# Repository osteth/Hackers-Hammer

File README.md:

# Hackers-Hammer
Hardware Hacking Multi-tool

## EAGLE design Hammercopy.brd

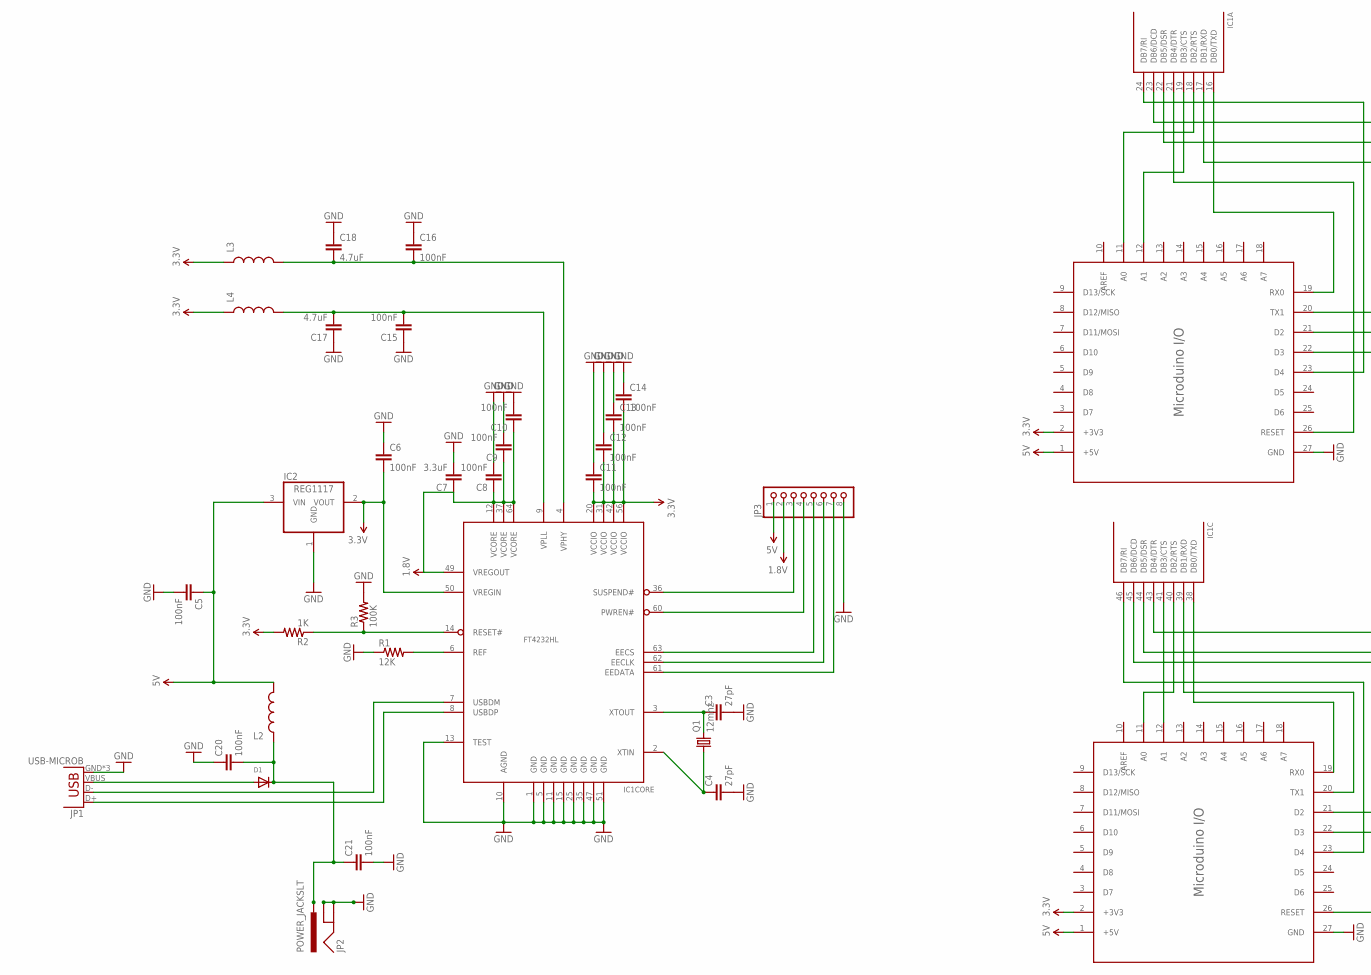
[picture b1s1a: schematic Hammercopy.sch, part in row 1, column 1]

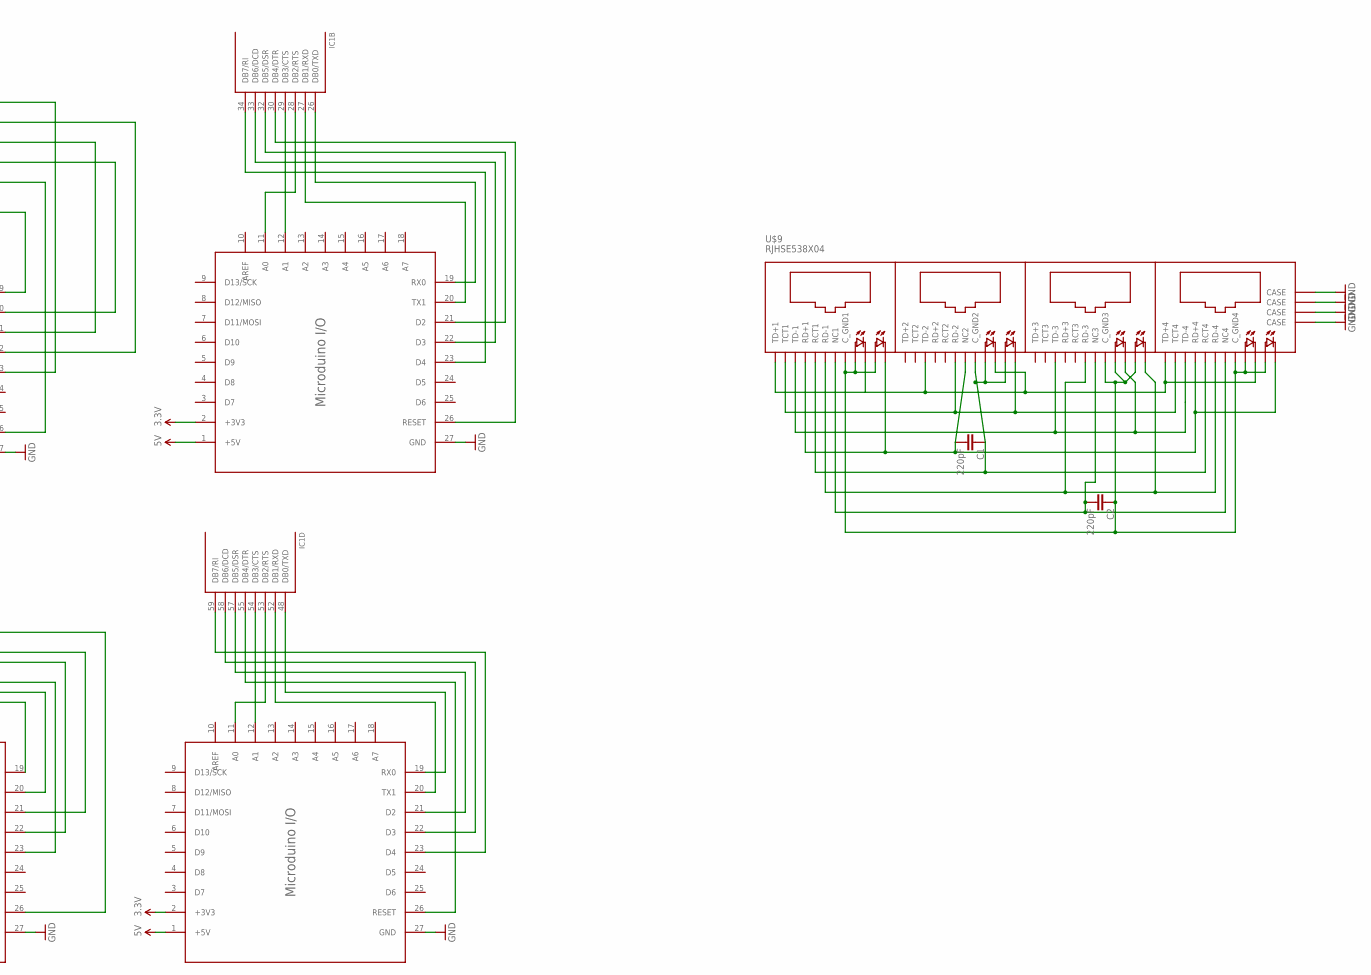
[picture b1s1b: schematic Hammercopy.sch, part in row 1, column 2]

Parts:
C1, C2: 220pF; 0402-CAP
C3, C4: 27pF; 0402-CAP
C5, C6, C8, C9, C10, C11, C12, C13, C14, C15, C16, C20, C21: 100nF; 0402-CAP
C7: 3.3uF; 0402-CAP
C17, C18: 4.7uF; 0402-CAP
D1: DIODESMA; SMADIODE
IC1: FT4232HL; LQFP64
IC2: REG1117; SOT223
JP1: USB-MICROB
JP2: POWER_JACKSLT; POWER_JACK_SLOT
JP3: PINHD-1X8BIG; 1X08-BIG
L2, L3, L4: INDUCTOR1206H*; INDUCTOR-1206
Q1: 12mhz; HC49UP
R1: 12K; 0402-RES
R2: 1K; 0402-RES
R3: 100K; 0402-RES
U$5, U$6, U$7, U$8: MICRODUINO_PING-MICRDUINO/1009-TEST; MICRODUINO_PIN-MICRODUINO-1009-TEST
U$9: RJHSE538X04

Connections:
1.8V: C7.1, C8.1, C9.1, C10.1, IC1.12 (VCORE), IC1.37 (VCORE), IC1.49 (VREGOUT), IC1.64 (VCORE), JP3.2
3.3V: C6.2, C11.2, C12.2, C13.2, C14.2, IC1.20 (VCCIO), IC1.31 (VCCIO), IC1.42 (VCCIO), IC1.56 (VCCIO), IC2.2 (VOUT), L3.P$1 (1), L4.P$1 (1), R2.2, U$5.2 (+3V3), U$6.2 (+3V3), U$7.2 (+3V3), U$8.2 (+3V3)
5V: C5.1, IC2.3 (VIN), JP3.1, L2.P$2 (2), U$5.1 (+5V), U$6.1 (+5V), U$7.1 (+5V), U$8.1 (+5V)
ASDF: C2.1, U$9.1-8 (C_GND1), U$9.1-10 (A2), U$9.1-12 (A1), U$9.3-8 (C_GND3), U$9.3-10 (A6), U$9.3-12 (A5)
GND: C3.2, C4.2, C5.2, C6.1, C7.2, C8.2, C9.2, C10.2, C11.1, C12.1, C13.1, C14.1, C15.1, C16.1, C17.1, C18.1, C20.1, C21.2, IC1.1 (GND), IC1.5 (GND), IC1.10 (AGND), IC1.11 (GND), IC1.13 (TEST), IC1.15 (GND), IC1.25 (GND), IC1.35 (GND), IC1.47 (GND), IC1.51 (GND), IC2.1 (GND), JP1.GND, JP1.MT1 (GND), JP1.MT2 (GND), JP2.GND@1 (GNDBREAK), JP2.GND@2 (GND), JP3.8, R1.1, R3.2, U$5.27 (GND), U$6.27 (GND), U$7.27 (GND), U$8.27 (GND), U$9.CASE@1 (CASE), U$9.CASE@2 (CASE), U$9.CASE@3 (CASE), U$9.CASE@4 (CASE)
INJECT: U$9.1-1 (TD+1), U$9.1-11 (C1), U$9.2-3 (TD-2), U$9.2-11 (C3)
unnamed: IC1.34 (DB7/RI), U$7.23 (D4)
unnamed: IC1.30 (DB4/DTR), U$7.26 (RESET)
unnamed: IC1.32 (DB5/DSR), U$7.21 (D2)
unnamed: IC1.21 (DB4/DTR), U$5.26 (RESET)
unnamed: IC1.16 (DB0/TXD), U$5.19 (RX0)
unnamed: IC1.41 (DB3/CTS), U$8.12 (A1)
unnamed: IC1.40 (DB2/RTS), U$8.11 (A0)
unnamed: IC1.7 (USBDM), JP1.D-
unnamed: IC1.6 (REF), R1.2
unnamed: IC1.14 (RESET#), R2.1, R3.1
unnamed: IC1.39 (DB1/RXD), U$8.20 (TX1)
unnamed: IC1.38 (DB0/TXD), U$8.19 (RX0)
unnamed: IC1.46 (DB7/RI), U$8.23 (D4)
unnamed: IC1.45 (DB6/DCD), U$8.22 (D3)
unnamed: IC1.36 (SUSPEND#), JP3.3
unnamed: IC1.60 (PWREN#), JP3.4
unnamed: IC1.17 (DB1/RXD), U$5.20 (TX1)
unnamed: IC1.63 (EECS), JP3.5
unnamed: IC1.62 (EECLK), JP3.6
unnamed: IC1.61 (EEDATA), JP3.7
unnamed: IC1.33 (DB6/DCD), U$7.22 (D3)
unnamed: IC1.18 (DB2/RTS), U$5.11 (A0)
unnamed: IC1.19 (DB3/CTS), U$5.12 (A1)
unnamed: IC1.22 (DB5/DSR), U$5.21 (D2)
unnamed: IC1.23 (DB6/DCD), U$5.22 (D3)
unnamed: IC1.24 (DB7/RI), U$5.23 (D4)
unnamed: IC1.44 (DB5/DSR), U$8.21 (D2)
unnamed: IC1.29 (DB3/CTS), U$7.12 (A1)
unnamed: IC1.28 (DB2/RTS), U$7.11 (A0)
unnamed: IC1.26 (DB0/TXD), U$7.19 (RX0)
unnamed: IC1.27 (DB1/RXD), U$7.20 (TX1)
unnamed: IC1.43 (DB4/DTR), U$8.26 (RESET)
unnamed: IC1.54 (DB3/CTS), U$6.12 (A1)
unnamed: IC1.53 (DB2/RTS), U$6.11 (A0)
unnamed: D1.A, JP1.VBUS
unnamed: U$9.1-2 (TCT1), U$9.2-6 (RD-2), U$9.2-9 (C4)
unnamed: U$9.1-3 (TD-1), U$9.3-3 (TD-3), U$9.3-11 (C5)
unnamed: C3.1, IC1.3 (XTOUT), Q1.2
unnamed: C4.1, IC1.2 (XTIN), Q1.1
unnamed: U$9.1-6 (RD-1), U$9.3-6 (RD-3), U$9.3-9 (C6)
unnamed: IC1.8 (USBDP), JP1.D+
unnamed: IC1.52 (DB1/RXD), U$6.20 (TX1)
unnamed: C1.2, U$9.1-4 (RD+1), U$9.1-9 (C2), U$9.2-7 (NC2)
unnamed: C1.1, U$9.1-5 (RCT1), U$9.2-8 (C_GND2)
unnamed: IC1.48 (DB0/TXD), U$6.19 (RX0)
unnamed: C2.2, U$9.1-7 (NC1), U$9.3-7 (NC3)
unnamed: IC1.55 (DB4/DTR), U$6.26 (RESET)
unnamed: IC1.57 (DB5/DSR), U$6.21 (D2)
unnamed: IC1.58 (DB6/DCD), U$6.22 (D3)
unnamed: IC1.59 (DB7/RI), U$6.23 (D4)
unnamed: U$9.4-1 (TD+4), U$9.4-11 (C7)
unnamed: C15.2, C17.2, IC1.9 (VPLL), L4.P$2 (2)
unnamed: C20.2, C21.1, D1.C, JP2.PWR, L2.P$1 (1)
unnamed: C16.2, C18.2, IC1.4 (VPHY), L3.P$2 (2)
unnamed: U$9.4-4 (RD+4), U$9.4-9 (C8)
unnamed: U$9.4-8 (C_GND4), U$9.4-10 (A8), U$9.4-12 (A7)
unnamed: U$9.2-10 (A4), U$9.2-12 (A3)

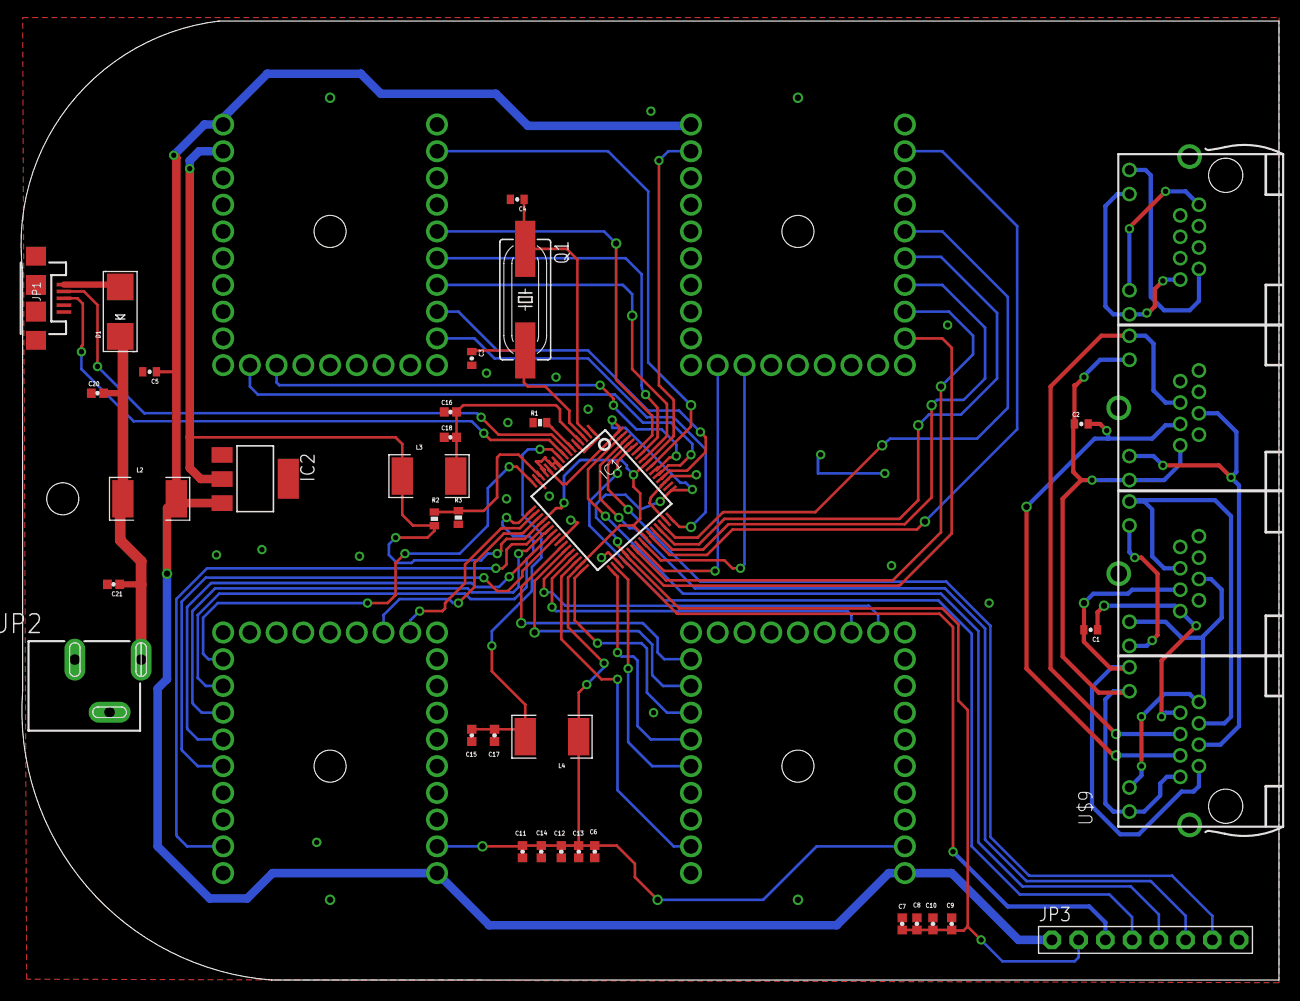
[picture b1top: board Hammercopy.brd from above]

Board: 2 copper layers, 119.5 x 91.1 mm, 44 parts (0 on the bottom side), 63 nets.

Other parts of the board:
U$1, U$2, U$3, U$4, U$10: STAND-OFF-TIGHT
U$11: A4L-LOC

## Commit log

2016-08-12 initial commit
    first design package upload

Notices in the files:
parts and their libraries:
SparkFun-Passives: Licensing: Creative Commons ShareAlike 4.0 International - https://creativecommons.org/licenses/by-sa/4.0
